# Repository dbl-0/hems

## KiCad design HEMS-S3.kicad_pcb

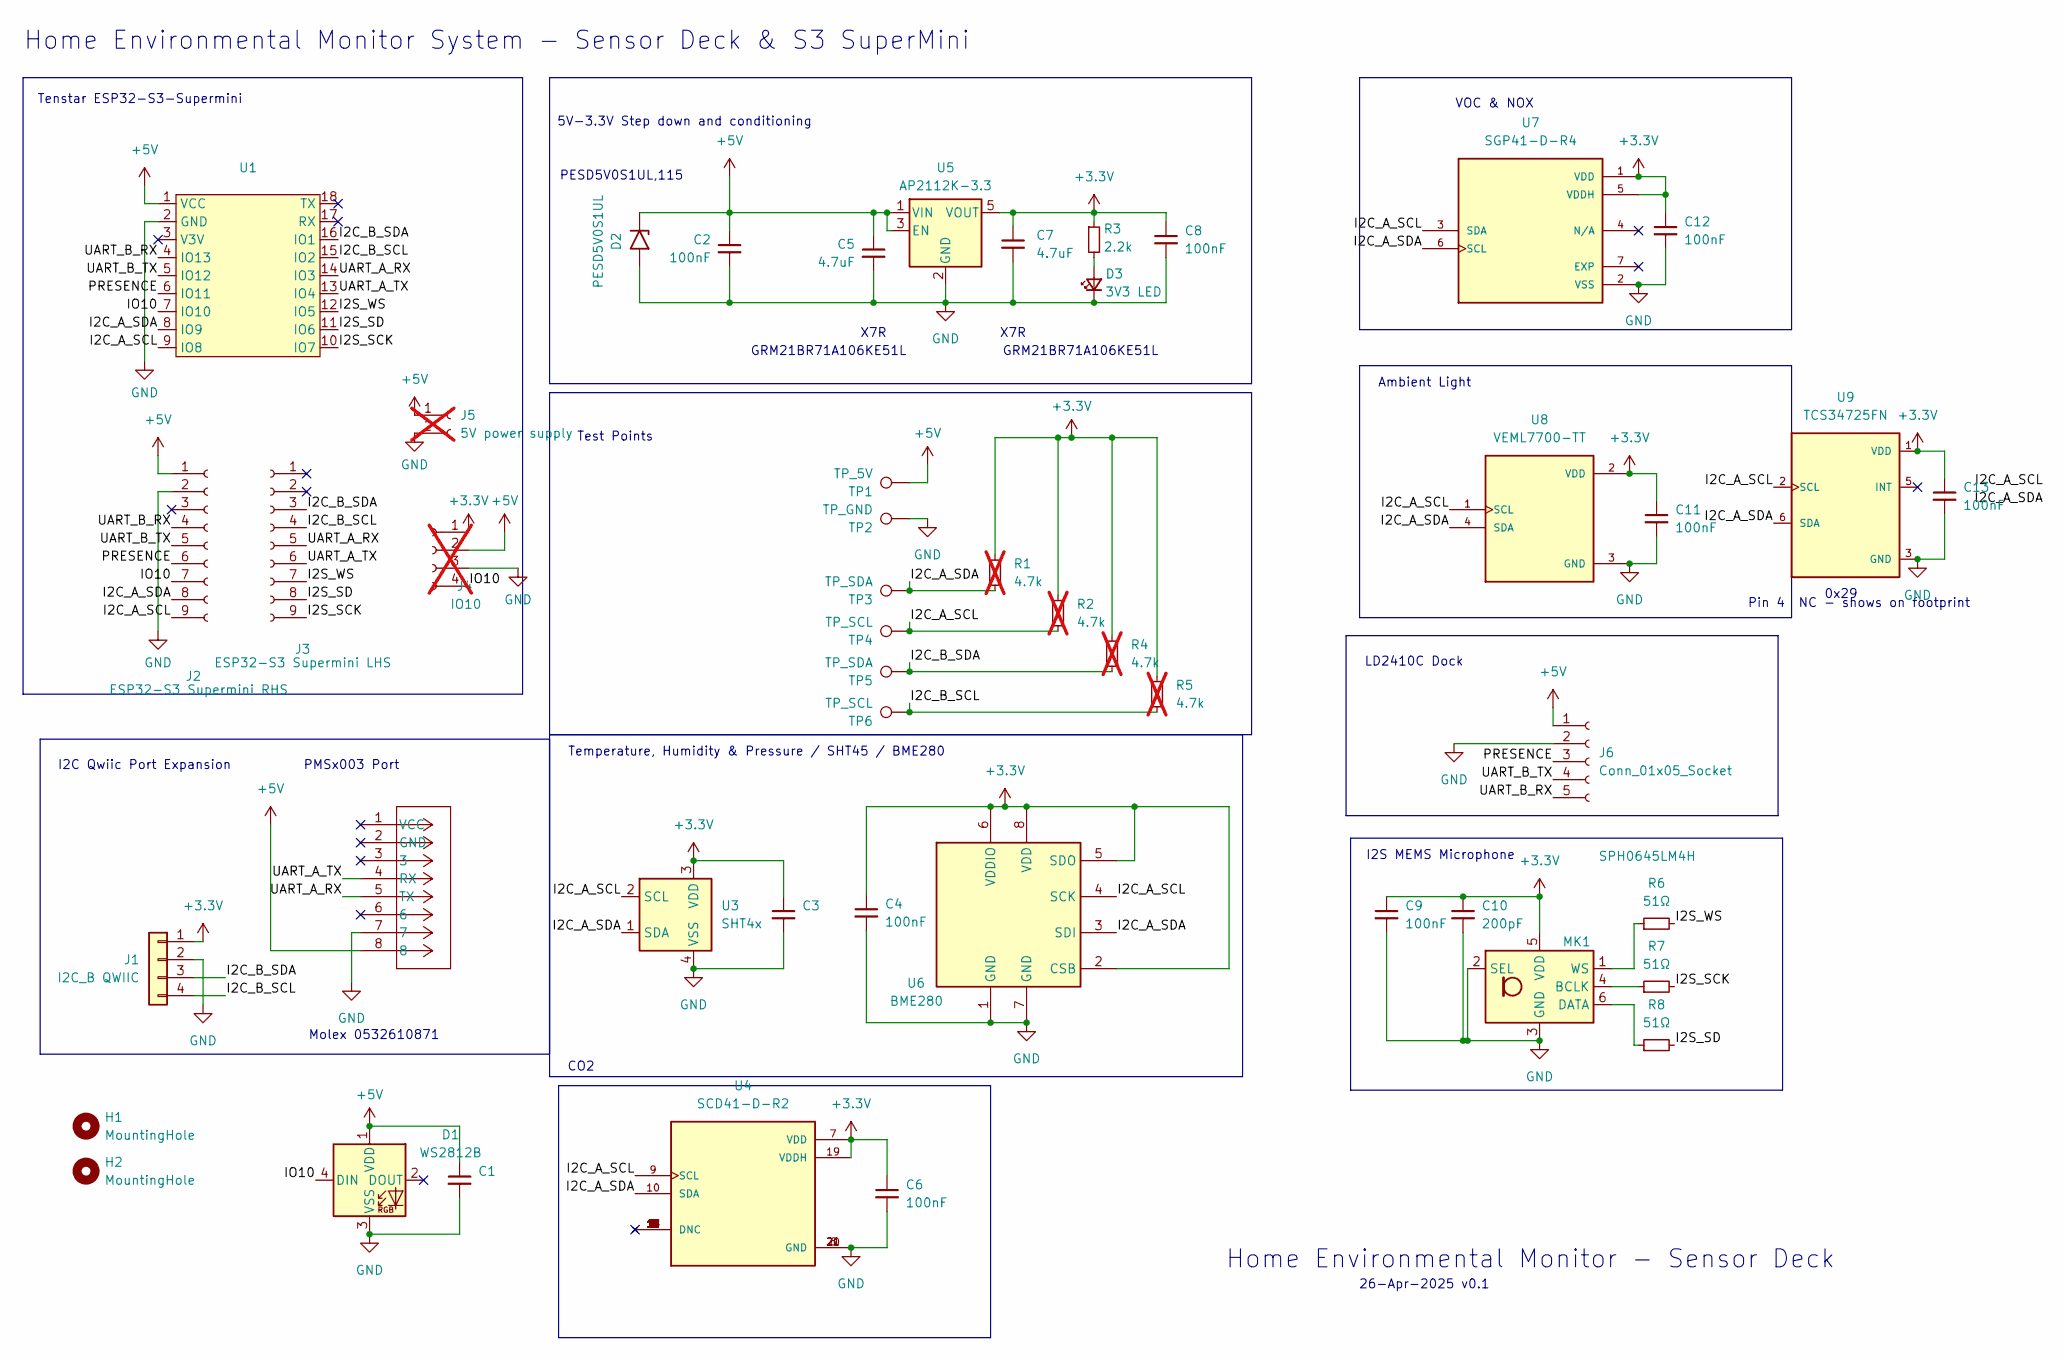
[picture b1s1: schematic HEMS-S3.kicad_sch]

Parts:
C1, C2, C3, C4, C6, C8, C9, C11, C12, C13: 100nF; C_0603_1608Metric
C5, C7: 4.7uF; C_0603_1608Metric
C10: 200pF; C_0603_1608Metric
D1: WS2812B; LED_WS2812B-Mini_PLCC4_3.5x3.5mm
D2: PESD5V0S1UL; D_SOD-323
D3: 3V3 LED; LED_0603_1608Metric
H1, H2: MountingHole; MountingHole_2.2mm_M2
J1: I2C_B QWIIC; JST_SH_SM04B-SRSS-TB_1x04-1MP_P1.00mm_Horizontal
J2: ESP32-S3 Supermini RHS; PinSocket_1x09_P2.54mm_Vertical
J3: ESP32-S3 Supermini LHS; PinSocket_1x09_P2.54mm_Vertical
J4: IO10; PinHeader_1x04_P2.54mm_Vertical; not fitted
J5: 5V power supply; PinHeader_1x02_P2.54mm_Vertical; not fitted
J6: Conn_01x05_Socket; PinSocket_1x05_P2.54mm_Vertical
MK1: SPH0645LM4H; Knowles_SPH0645LM4H-6_3.5x2.65mm
R1, R2, R4, R5: 4.7k; R_0603_1608Metric; not fitted
R3: 2.2k; R_0603_1608Metric
R6, R7, R8: 51Ω; R_0603_1608Metric
TP1: TP_5V; TestPoint_Pad_1.0x1.0mm
TP2: TP_GND; TestPoint_Pad_1.0x1.0mm
TP3, TP5: TP_SDA; TestPoint_Pad_1.0x1.0mm
TP4, TP6: TP_SCL; TestPoint_Pad_1.0x1.0mm
U1: Tenstar-ESP32-S3-SuperMini
U2: 0532610871; CONN_532610001-SD_08_MOL
U3: SHT4x; Sensirion_DFN-4_1.5x1.5mm_P0.8mm_SHT4x_NoCentralPad
U4: SCD41-D-R2; XDCR_SCD41-D-R2; PARTREV 1.2
U5: AP2112K-3.3; SOT-23-5
U6: BME280; Bosch_LGA-8_2.5x2.5mm_P0.65mm_ClockwisePinNumbering
U7: SGP41-D-R4; XDCR_SGP41-D-R4; PARTREV 1.0; DigiKey_Part_Number 1649-SGP41-D-R4TR-ND
U8: VEML7700-TT; XDCR_VEML7700-TT; PARTREV 1.6; DigiKey_Part_Number 751-VEML7700-TTTR-ND
U9: TCS34725FN; SON65P200X240X70-6N; PARTREV 1-02

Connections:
+3.3V: C3.1, C4.1, C6.1, C7.1, C8.1, C9.1, C10.1, C11.1, C12.1, C13.1, J1.1, J4.1, MK1.5 (VDD), R1.1, R2.1, R3.1, R4.1, R5.1, U3.3 (VDD), U4.7 (VDD), U4.19 (VDDH), U5.5 (VOUT), U6.2 (CSB), U6.5 (SDO), U6.6 (VDDIO), U6.8 (VDD), U7.1 (VDD), U7.5 (VDDH), U8.2 (VDD), U9.1 (VDD)
+5V: C1.1, C2.1, C5.1, D1.1 (VDD), D2.1 (A1), J2.1, J4.2, J5.1, J6.1 (VCC), TP1.1, U1.1 (VCC), U2.8, U5.1 (VIN), U5.3 (EN)
/I2C_A_SCL: J2.9, R2.2, TP4.1, U1.9 (IO8), U3.2 (SCL), U4.9 (SCL), U6.4 (SCK), U7.3 (SDA), U8.1 (SCL), U9.2 (SCL)
/I2C_A_SDA: J2.8, R1.2, TP3.1, U1.8 (IO9), U3.1 (SDA), U4.10 (SDA), U6.3 (SDI), U7.6 (SCL), U8.4 (SDA), U9.6 (SDA)
/I2C_B_SCL: J1.4, J3.4, R5.2, TP6.1, U1.15 (IO2)
/I2C_B_SDA: J1.3, J3.3, R4.2, TP5.1, U1.16 (IO1)
/I2S_SCK: J3.9, R7.2, U1.10 (IO7)
/I2S_SD: J3.8, R8.2, U1.11 (IO6)
/I2S_WS: J3.7, R6.2, U1.12 (IO5)
/IO10: D1.4 (DIN), J2.7, J4.4, U1.7 (IO10)
/PRESENCE: J2.6, J6.3 (Out), U1.6 (IO11)
/UART_A_RX: J3.5, U1.14 (IO3), U2.5 (TX)
/UART_A_TX: J3.6, U1.13 (IO4), U2.4 (RX)
/UART_B_RX: J2.4, J6.5 (TX), U1.4 (IO13)
/UART_B_TX: J2.5, J6.4 (RX), U1.5 (IO12)
GND: C1.2, C2.2, C3.2, C4.2, C5.2, C6.2, C7.2, C8.2, C9.2, C10.2, C11.2, C12.2, C13.2, D1.3 (VSS), D2.2 (A2), D3.1 (K), J1.2, J2.2, J4.3, J5.2, J6.2 (GND), MK1.2 (SEL), MK1.3 (GND), TP2.1, U1.2 (GND), U2.7, U3.4 (VSS), U4.6 (GND), U4.20 (GND), U4.21 (GND), U5.2 (GND), U6.1 (GND), U6.7 (GND), U7.2 (VSS), U8.3 (GND), U9.3 (GND)
unnamed: D3.2 (A), R3.2
unnamed: MK1.4 (BCLK), R7.1
unnamed: MK1.6 (DATA), R8.1
unnamed: MK1.1 (WS), R6.1

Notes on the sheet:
Home Environmental Monitor System - Sensor Deck & S3 SuperMini
LD2410C Dock
Pin 4 NC - shows on footprint
5V-3.3V Step down and conditioning
PMSx003 Port
Tenstar ESP32-S3-Supermini
VOC & NOX
Test Points
GRM21BR71A106KE51L
PESD5V0S1UL,115
Ambient Light
26-Apr-2025 v0.1
I2C Qwiic Port Expansion
X7R
0x29
Home Environmental Monitor - Sensor Deck
Molex 0532610871
CO2
I2S MEMS Microphone
Temperature, Humidity & Pressure / SHT45 / BME280

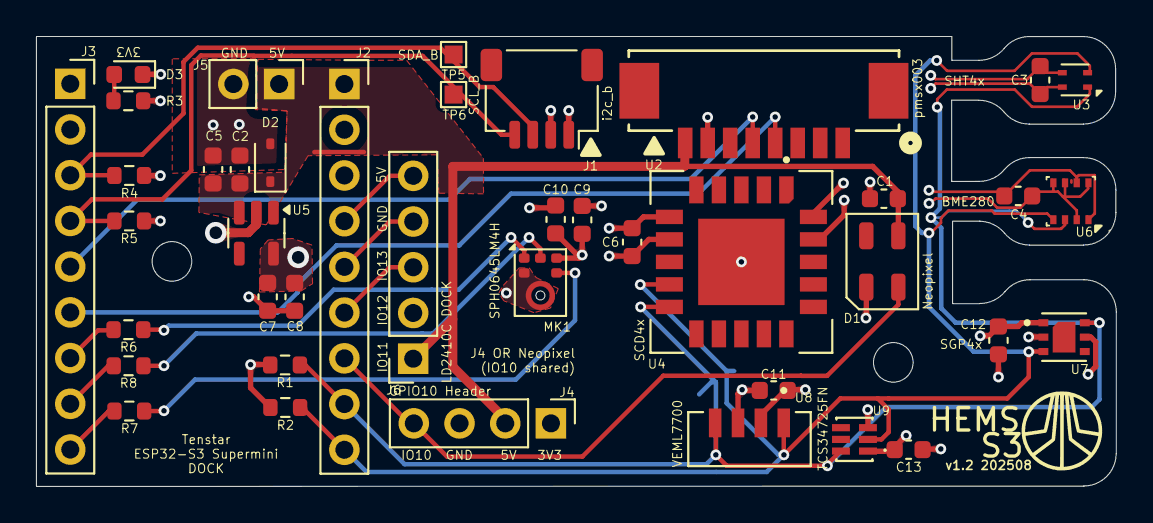
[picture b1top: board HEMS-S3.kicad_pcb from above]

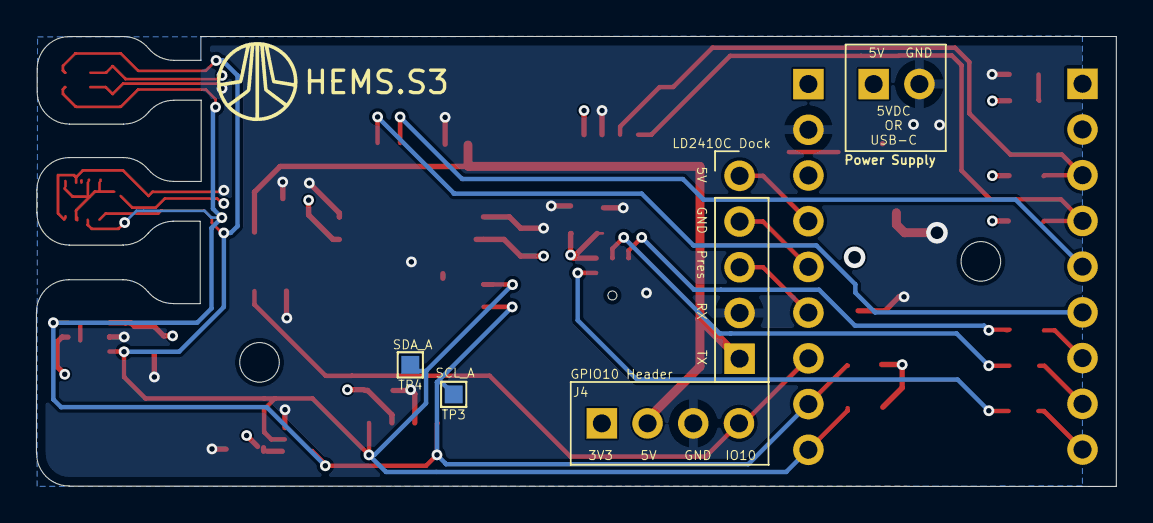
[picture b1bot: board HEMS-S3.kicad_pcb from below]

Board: 4 copper layers, 60.0 x 25.0 mm, 45 parts (2 on the bottom side), 20 nets.

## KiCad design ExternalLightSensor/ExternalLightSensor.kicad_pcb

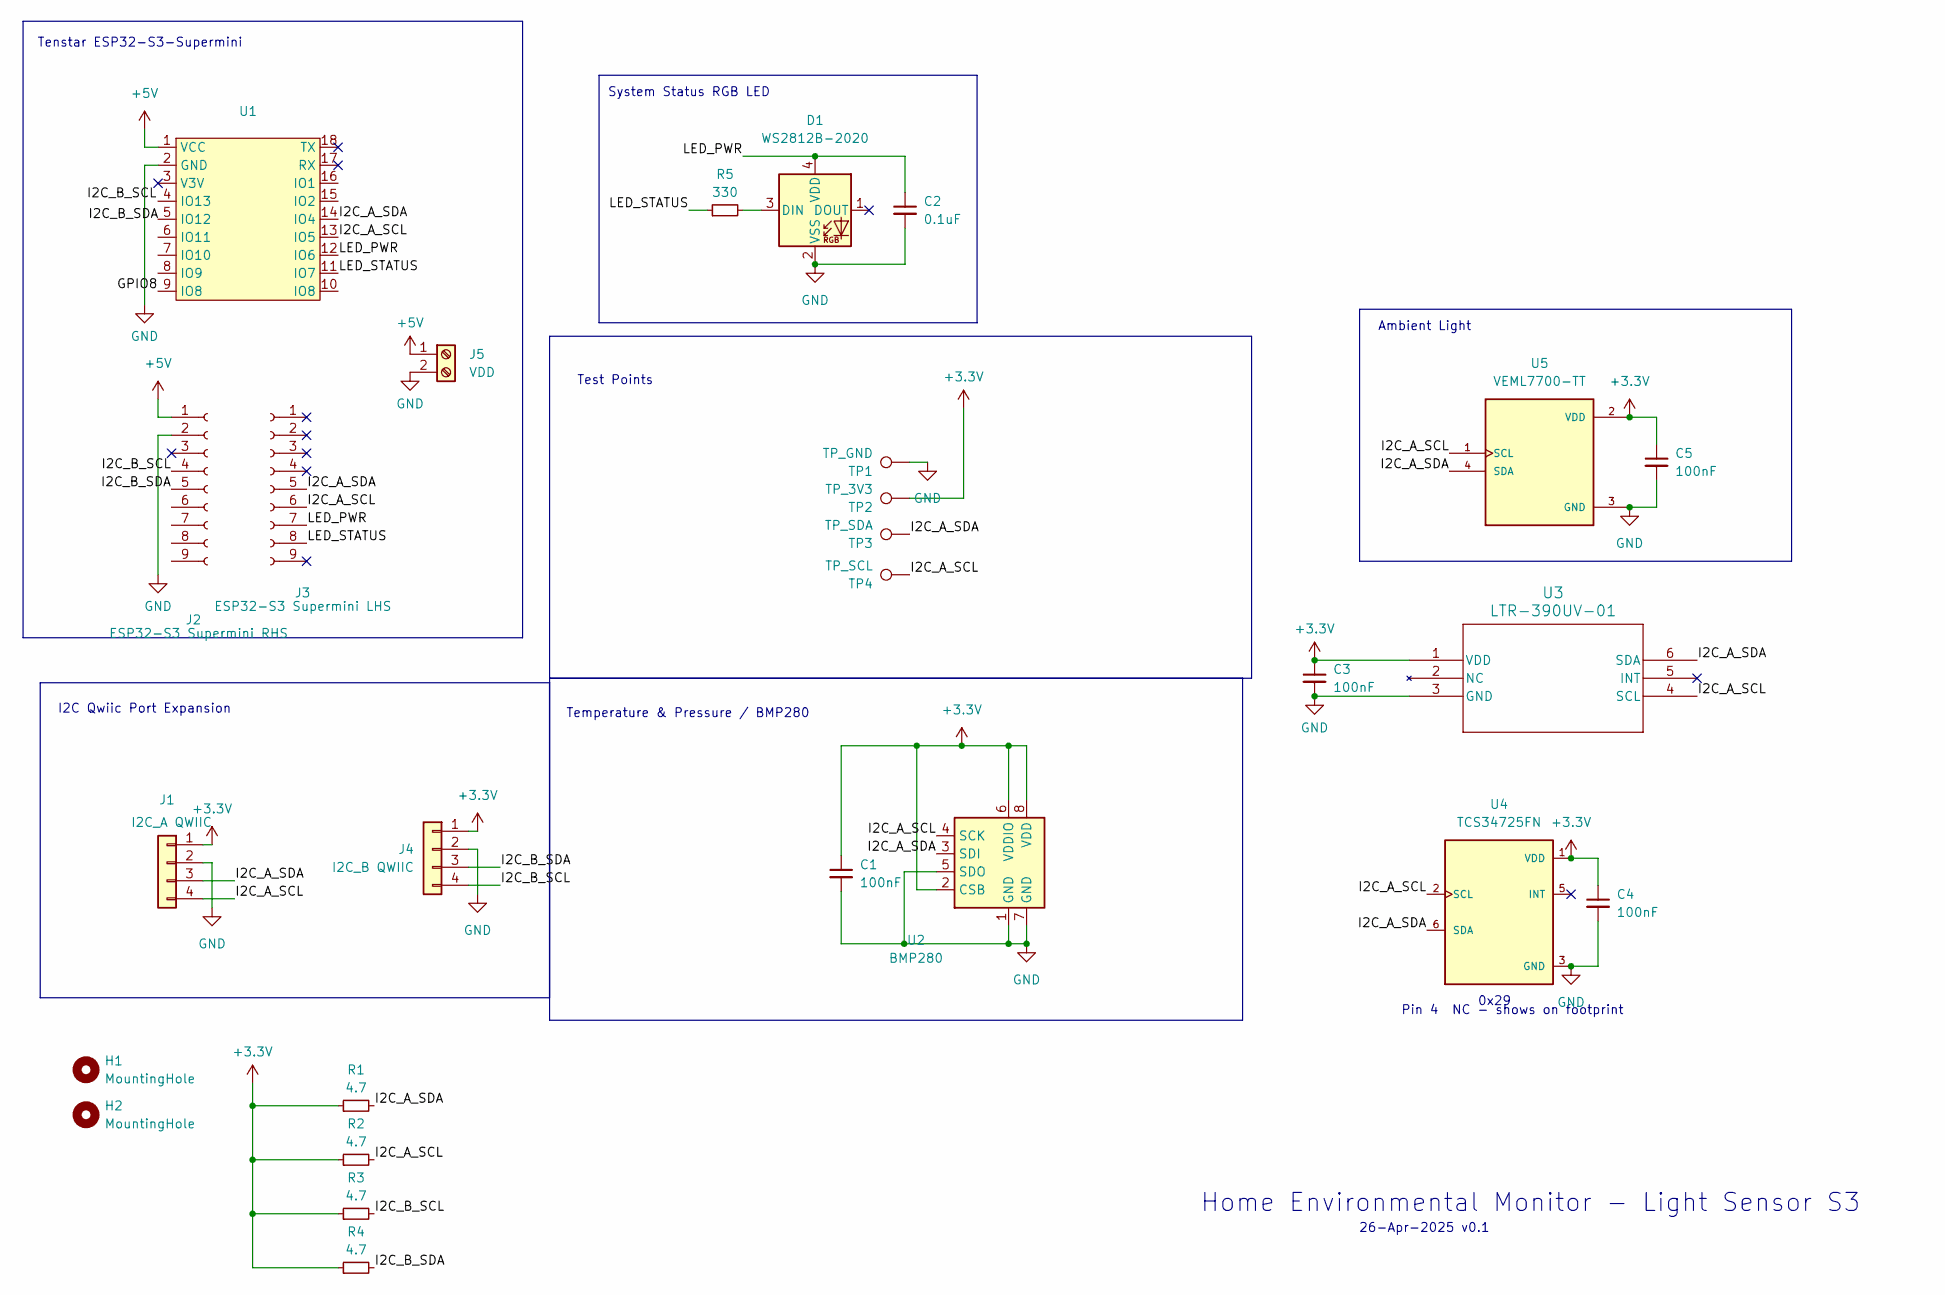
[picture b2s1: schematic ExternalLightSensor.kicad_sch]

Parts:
C1, C3, C4, C5: 100nF; C_0201_0603Metric
C2: 0.1uF; C_0201_0603Metric; LCSC C49678
D1: WS2812B-2020; LED_WS2812B-2020_PLCC4_2.0x2.0mm; LCSC C965555
H1, H2: MountingHole; MountingHole_2.2mm_M2
J1: I2C_A QWIIC; JST_SH_SM04B-SRSS-TB_1x04-1MP_P1.00mm_Horizontal
J2: ESP32-S3 Supermini RHS; PinSocket_1x09_P2.54mm_Vertical
J3: ESP32-S3 Supermini LHS; PinSocket_1x09_P2.54mm_Vertical
J4: I2C_B QWIIC; JST_SH_SM04B-SRSS-TB_1x04-1MP_P1.00mm_Horizontal
J5: VDD; TerminalBlock_Phoenix_MPT-0,5-2-2.54_1x02_P2.54mm_Horizontal
R1, R2, R3, R4: 4.7; R_0201_0603Metric; LCSC C17630
R5: 330; R_0201_0603Metric; LCSC C17630
TP1: TP_GND; TestPoint_Pad_1.0x1.0mm
TP2: TP_3V3; TestPoint_Pad_1.0x1.0mm
TP3: TP_SDA; TestPoint_Pad_1.0x1.0mm
TP4: TP_SCL; TestPoint_Pad_1.0x1.0mm
U1: Tenstar-ESP32-S3-SuperMini
U2: BMP280; Bosch_LGA-8_2x2.5mm_P0.65mm_ClockwisePinNumbering
U3: LTR-390UV-01; SMD6_LTR-390UV-01_LTO
U4: TCS34725FN; SON65P200X240X70-6N; PARTREV 1-02
U5: VEML7700-TT; XDCR_VEML7700-TT; PARTREV 1.6; DigiKey_Part_Number 751-VEML7700-TTTR-ND

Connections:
+3.3V: C1.1, C3.1, C4.1, C5.1, J1.1, J4.1, R1.1, R2.1, R3.1, R4.1, TP2.1, U2.2 (CSB), U2.6 (VDDIO), U2.8 (VDD), U3.1 (VDD), U4.1 (VDD), U5.2 (VDD)
+5V: J2.1, J5.1, U1.1 (VCC)
/I2C_A_SCL: J1.4, J3.6, R2.2, TP4.1, U1.13 (IO5), U2.4 (SCK), U3.4 (SCL), U4.2 (SCL), U5.1 (SCL)
/I2C_A_SDA: J1.3, J3.5, R1.2, TP3.1, U1.14 (IO4), U2.3 (SDI), U3.6 (SDA), U4.6 (SDA), U5.4 (SDA)
/I2C_B_SCL: J2.4, J4.4, R3.2
/I2C_B_SDA: J2.5, J4.3, R4.2
/LED_PWR: C2.1, D1.4 (VDD), J3.7, U1.12 (IO6)
/LED_STATUS: J3.8, R5.1, U1.11 (IO7)
GND: C1.2, C2.2, C3.2, C4.2, C5.2, D1.2 (VSS), J1.2, J2.2, J4.2, J5.2, TP1.1, U1.2 (GND), U2.1 (GND), U2.5 (SDO), U2.7 (GND), U3.3 (GND), U4.3 (GND), U5.3 (GND)
unnamed: D1.3 (DIN), R5.2

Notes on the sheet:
0x29
Home Environmental Monitor - Light Sensor S3
Tenstar ESP32-S3-Supermini
Temperature & Pressure / BMP280
I2C Qwiic Port Expansion
Test Points
System Status RGB LED
Ambient Light
Pin 4 NC - shows on footprint
26-Apr-2025 v0.1

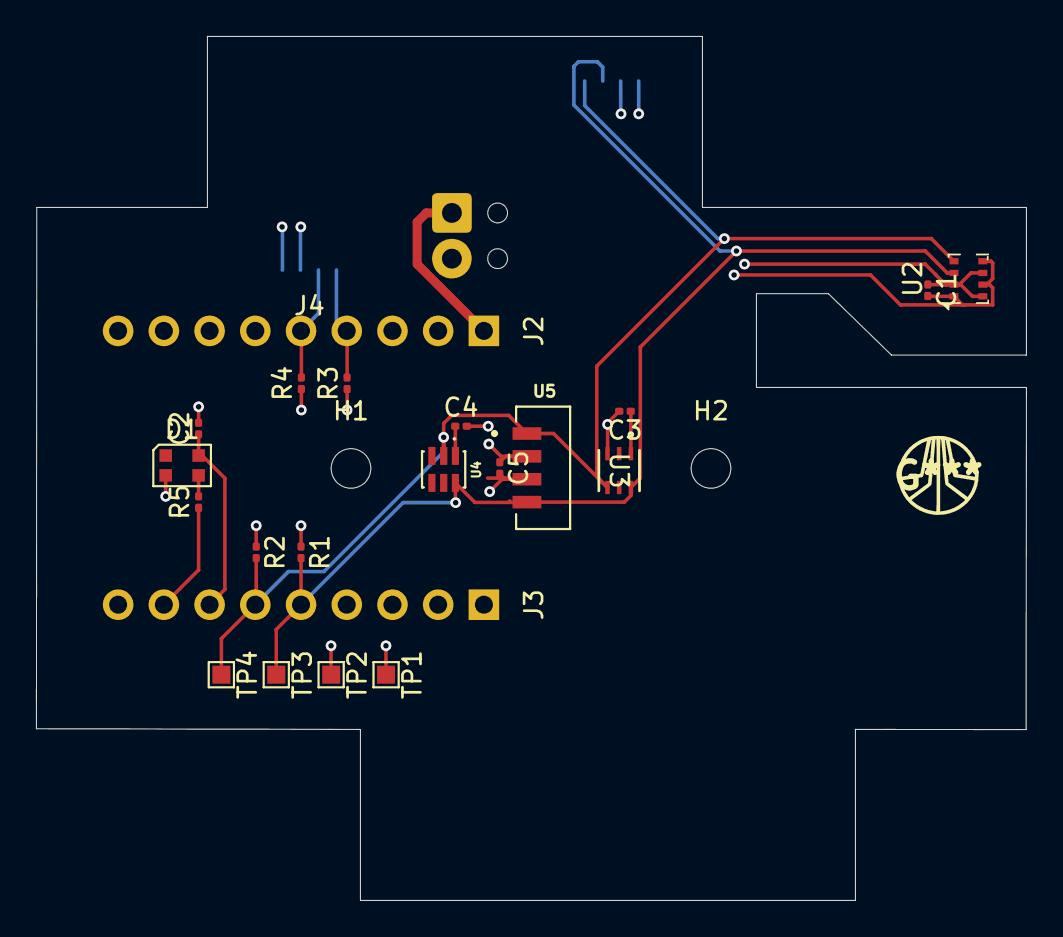
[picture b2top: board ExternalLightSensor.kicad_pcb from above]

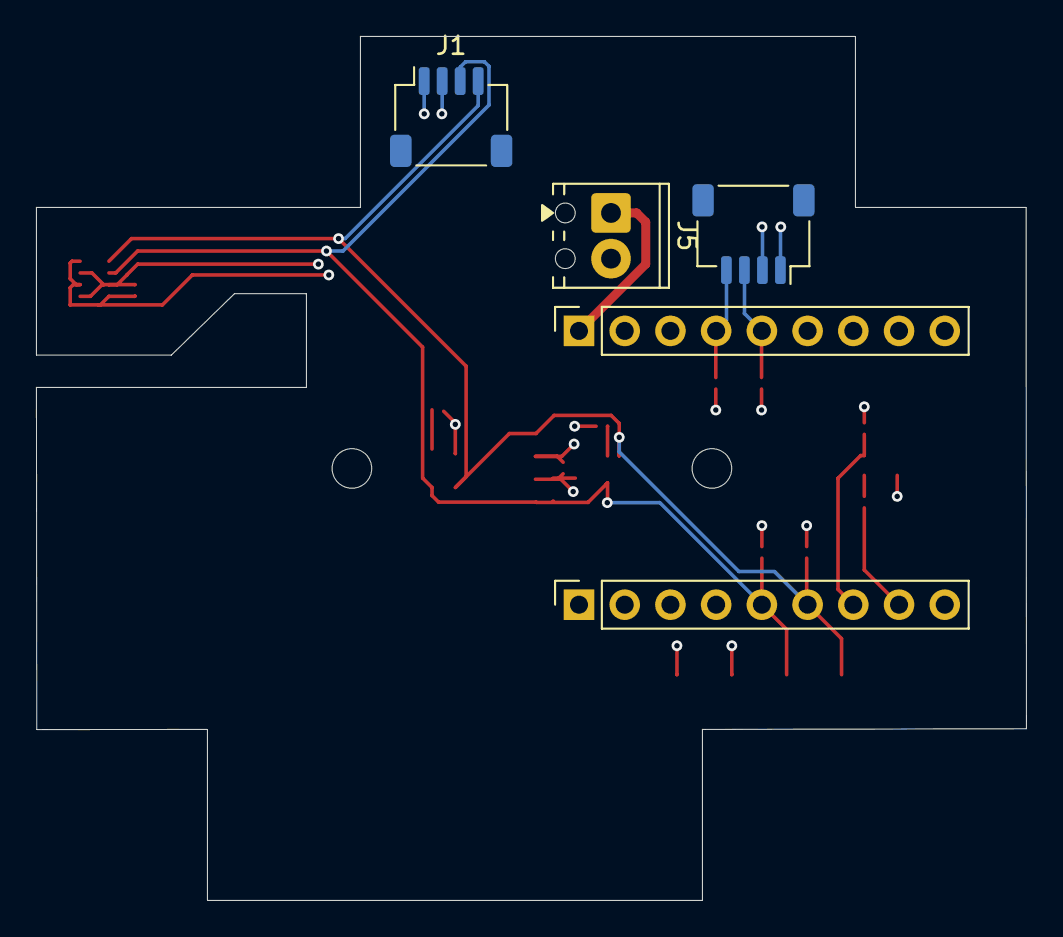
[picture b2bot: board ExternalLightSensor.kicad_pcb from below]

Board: 4 copper layers, 55.0 x 48.0 mm, 26 parts (5 on the bottom side), 10 nets.

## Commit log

2025-10-27 Initial commit of HEMS-S3
2025-10-27 Remove ExternalLightSensor files
